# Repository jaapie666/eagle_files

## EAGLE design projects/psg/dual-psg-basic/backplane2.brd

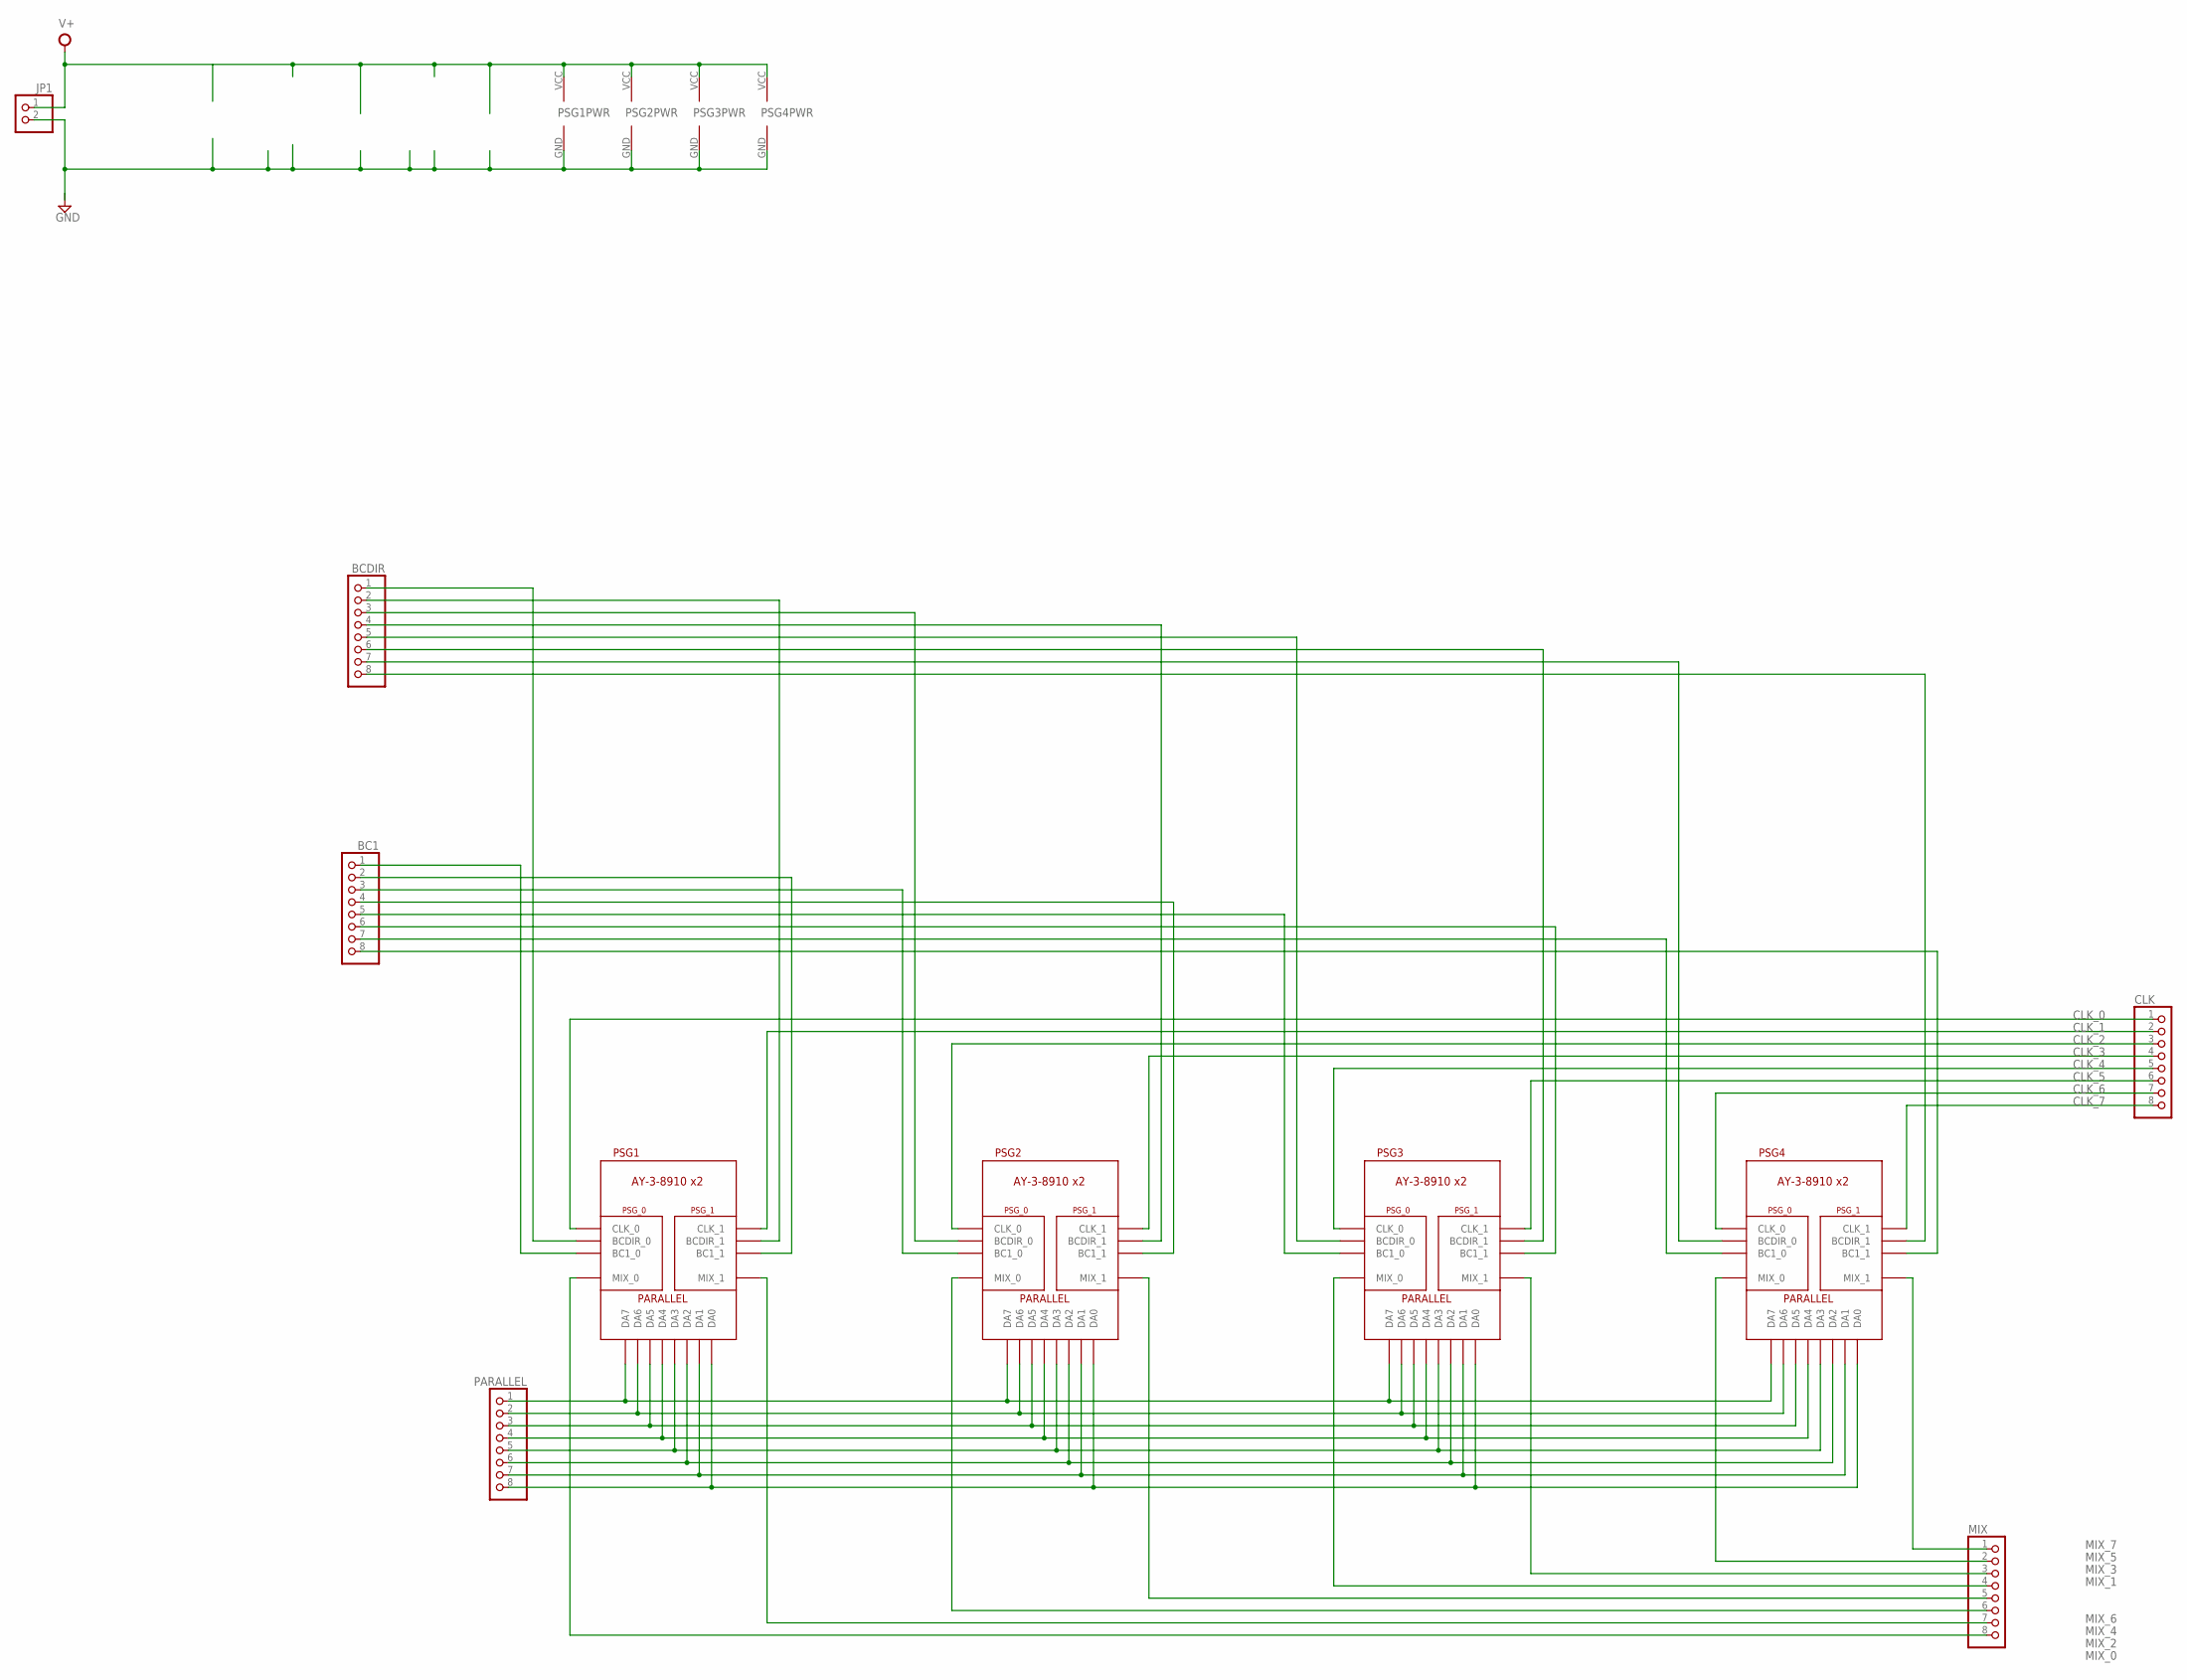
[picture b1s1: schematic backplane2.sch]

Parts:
BC1: PINHD-1X8; 1X08
BCDIR: PINHD-1X8; 1X08
CLK: PINHD-1X8; 1X08
JP1: PINHD-1X2; 1X02
MIX: PINHD-1X8; 1X08
PARALLEL: PINHD-1X8; 1X08
PSG1, PSG2, PSG3, PSG4: DUAL_PSG_DAUGHTER

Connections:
3: BCDIR.4, PSG2.BCDIR_1
BC1_0: BC1.1, PSG1.BC1_0
BC1_1: BC1.2, PSG1.BC1_1
BC1_2: BC1.3, PSG2.BC1_0
BC1_3: BC1.4, PSG2.BC1_1
BC1_4: BC1.5, PSG3.BC1_0
BC1_5: BC1.6, PSG3.BC1_1
BC1_6: BC1.7, PSG4.BC1_0
BC1_7: BC1.8, PSG4.BC1_1
BCDIR_0: BCDIR.1, PSG1.BCDIR_0
BCDIR_1: BCDIR.2, PSG1.BCDIR_1
BCDIR_2: BCDIR.3, PSG2.BCDIR_0
BCDIR_4: BCDIR.5, PSG3.BCDIR_0
BCDIR_5: BCDIR.6, PSG3.BCDIR_1
BCDIR_6: BCDIR.7, PSG4.BCDIR_0
BCDIR_7: BCDIR.8, PSG4.BCDIR_1
CLK_0: CLK.1, PSG1.CLK_0
CLK_1: CLK.2, PSG1.CLK_1
CLK_2: CLK.3, PSG2.CLK_0
CLK_3: CLK.4, PSG2.CLK_1
CLK_4: CLK.5, PSG3.CLK_0
CLK_5: CLK.6, PSG3.CLK_1
CLK_6: CLK.7, PSG4.CLK_0
CLK_7: CLK.8, PSG4.CLK_1
DA0: PARALLEL.8, PSG1.DA0, PSG2.DA0, PSG3.DA0, PSG4.DA0
DA1: PARALLEL.7, PSG1.DA1, PSG2.DA1, PSG3.DA1, PSG4.DA1
DA2: PARALLEL.6, PSG1.DA2, PSG2.DA2, PSG3.DA2, PSG4.DA2
DA3: PARALLEL.5, PSG1.DA3, PSG2.DA3, PSG3.DA3, PSG4.DA3
DA4: PARALLEL.4, PSG1.DA4, PSG2.DA4, PSG3.DA4, PSG4.DA4
DA5: PARALLEL.3, PSG1.DA5, PSG2.DA5, PSG3.DA5, PSG4.DA5
DA6: PARALLEL.2, PSG1.DA6, PSG2.DA6, PSG3.DA6, PSG4.DA6
DA7: PARALLEL.1, PSG1.DA7, PSG2.DA7, PSG3.DA7, PSG4.DA7
GND: JP1.2, PSG1.GND, PSG2.GND, PSG3.GND, PSG4.GND
MIX_0: MIX.8, PSG1.MIX_0
MIX_1: MIX.7, PSG1.MIX_1
MIX_2: MIX.6, PSG2.MIX_0
MIX_3: MIX.5, PSG2.MIX_1
MIX_4: MIX.4, PSG3.MIX_0
MIX_5: MIX.3, PSG3.MIX_1
MIX_6: MIX.2, PSG4.MIX_0
MIX_7: MIX.1, PSG4.MIX_1
V+: JP1.1, PSG1.VCC, PSG2.VCC, PSG3.VCC, PSG4.VCC

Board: 2 copper layers, 10 parts (0 on the bottom side), 42 nets, no tracks yet.

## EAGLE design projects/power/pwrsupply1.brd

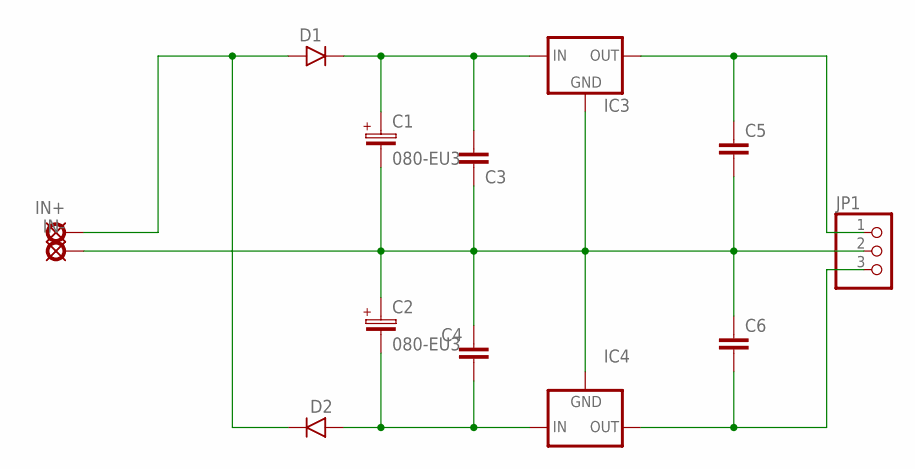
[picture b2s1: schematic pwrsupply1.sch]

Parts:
C1, C2: 080-EU3; 080_035_3
C3, C4: 070X0303; 070X030_3
C5: 070X0305; 070X030_5
C6: 070X0302; 070X030
D1, D2: 1N400X.4; DO41-4
IC3: 78XXL
IC4: 79XXL
IN+: PAD8; OCTOGON
IN-: PAD8; OCTOGON
JP1: PINHD-1X3; 1X03

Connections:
+15: C5.1, IC3.OUT, JP1.1
-15: C6.2, IC4.OUT, JP1.3
GND: C1.-, C2.+, C3.1, C4.1, C5.2, C6.1, IC3.GND, IC4.GND, IN-.1, JP1.2
unnamed: D1.A, D2.C, IN+.1
unnamed: C1.+, C3.2, D1.C, IC3.IN
unnamed: C2.-, C4.2, D2.A, IC4.IN

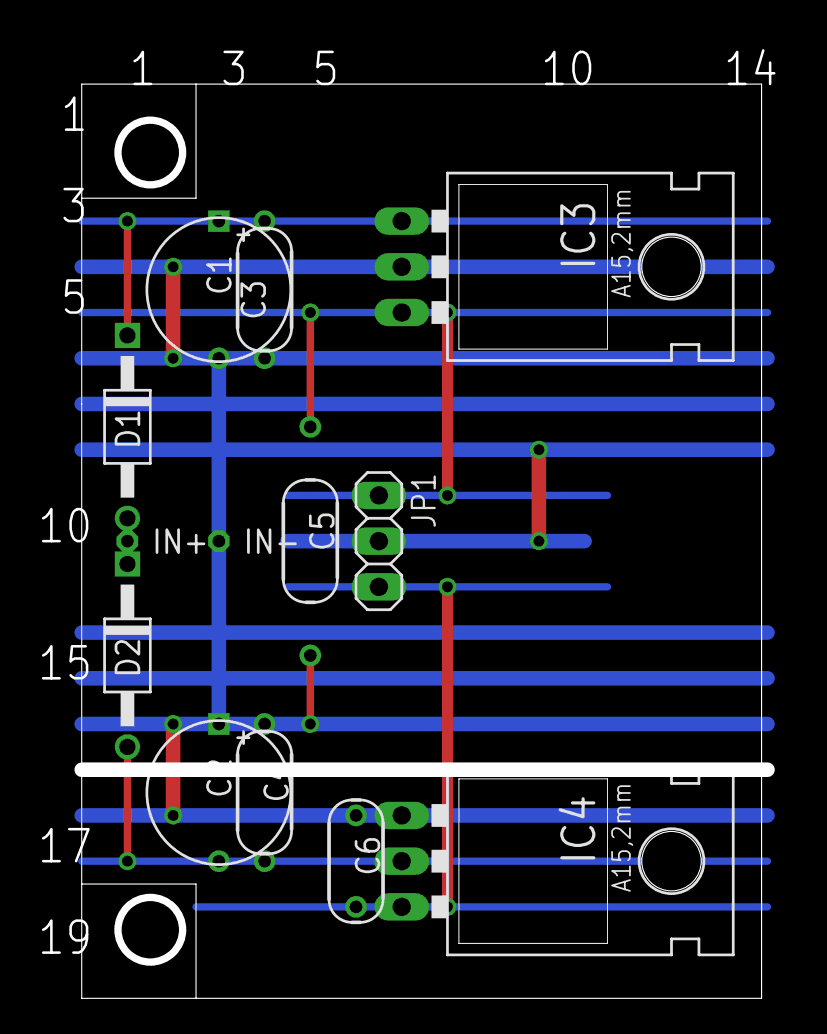
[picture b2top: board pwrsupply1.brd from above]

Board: 2 copper layers, 37.8 x 50.8 mm, 13 parts (0 on the bottom side), 6 nets.

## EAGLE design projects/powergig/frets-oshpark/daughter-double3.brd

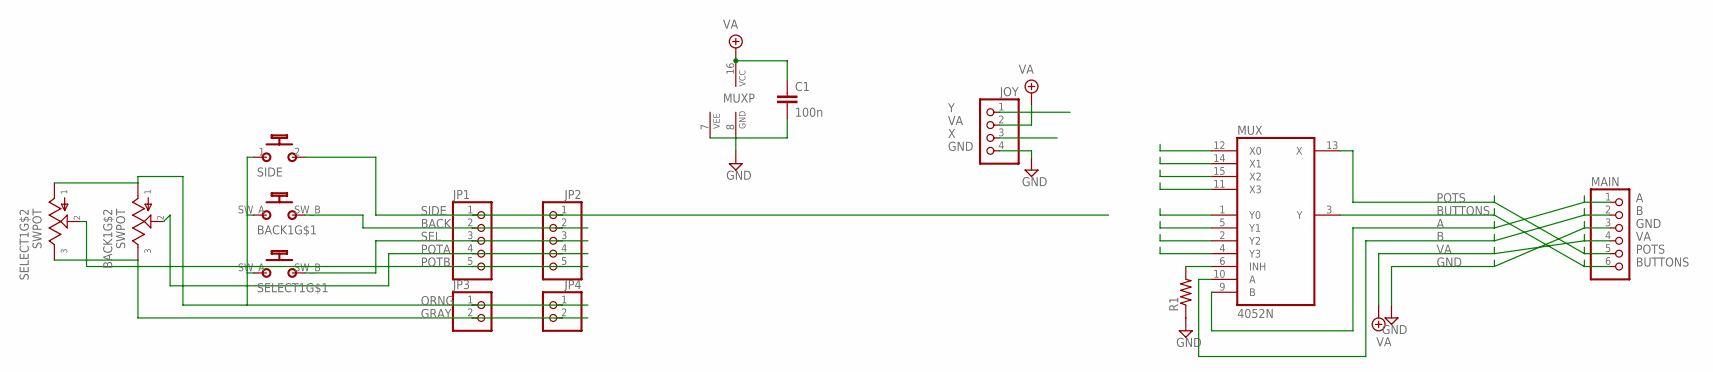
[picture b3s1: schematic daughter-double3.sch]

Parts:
BACK1: SWPOT
C1: 100n; 050X030_050_3
JOY: PINHD-1X4; 1X04
JP1, JP2: PINHD-1X5; 1X05
JP3, JP4: PINHD-1X2; 1X02
MAIN: PINHD-1X6; 1X06
MUX: 4052N; DIL16
R1: 6MM.1; R0207/1V
SELECT1: SWPOT
SIDE: MOMENTARYSPST1; SPST

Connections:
A: MAIN.1, MUX.9 (B)
B: MAIN.2, MUX.10 (A)
BACK: BACK1.SW_B (B_B), JP1.2, JP2.2
BUTTONS: MAIN.6, MUX.3 (Y)
GND: C1.2, JOY.4, MAIN.3, MUX.7 (VEE), MUX.8 (GND), R1.1
GRAY: BACK1.POT_A, JP3.2, JP4.2, SELECT1.POT_A
unnamed: MUX.6 (INH), R1.2
ORNG: BACK1.POT_B, BACK1.SW_A (B_A), JP3.1, JP4.1, SELECT1.POT_B, SELECT1.SW_A (B_A), SIDE.1
POTA: BACK1.POT_W, JP1.4, JP2.4
POTB: JP1.5, JP2.5, SELECT1.POT_W
POTS: MAIN.5, MUX.13 (X)
SEL: JP1.3, JP2.3, SELECT1.SW_B (B_B)
SIDE: JP2.1, SIDE.2 (S)
VA: C1.1, JOY.2, MAIN.4, MUX.16 (VCC)
X: JOY.1
Y: JOY.3

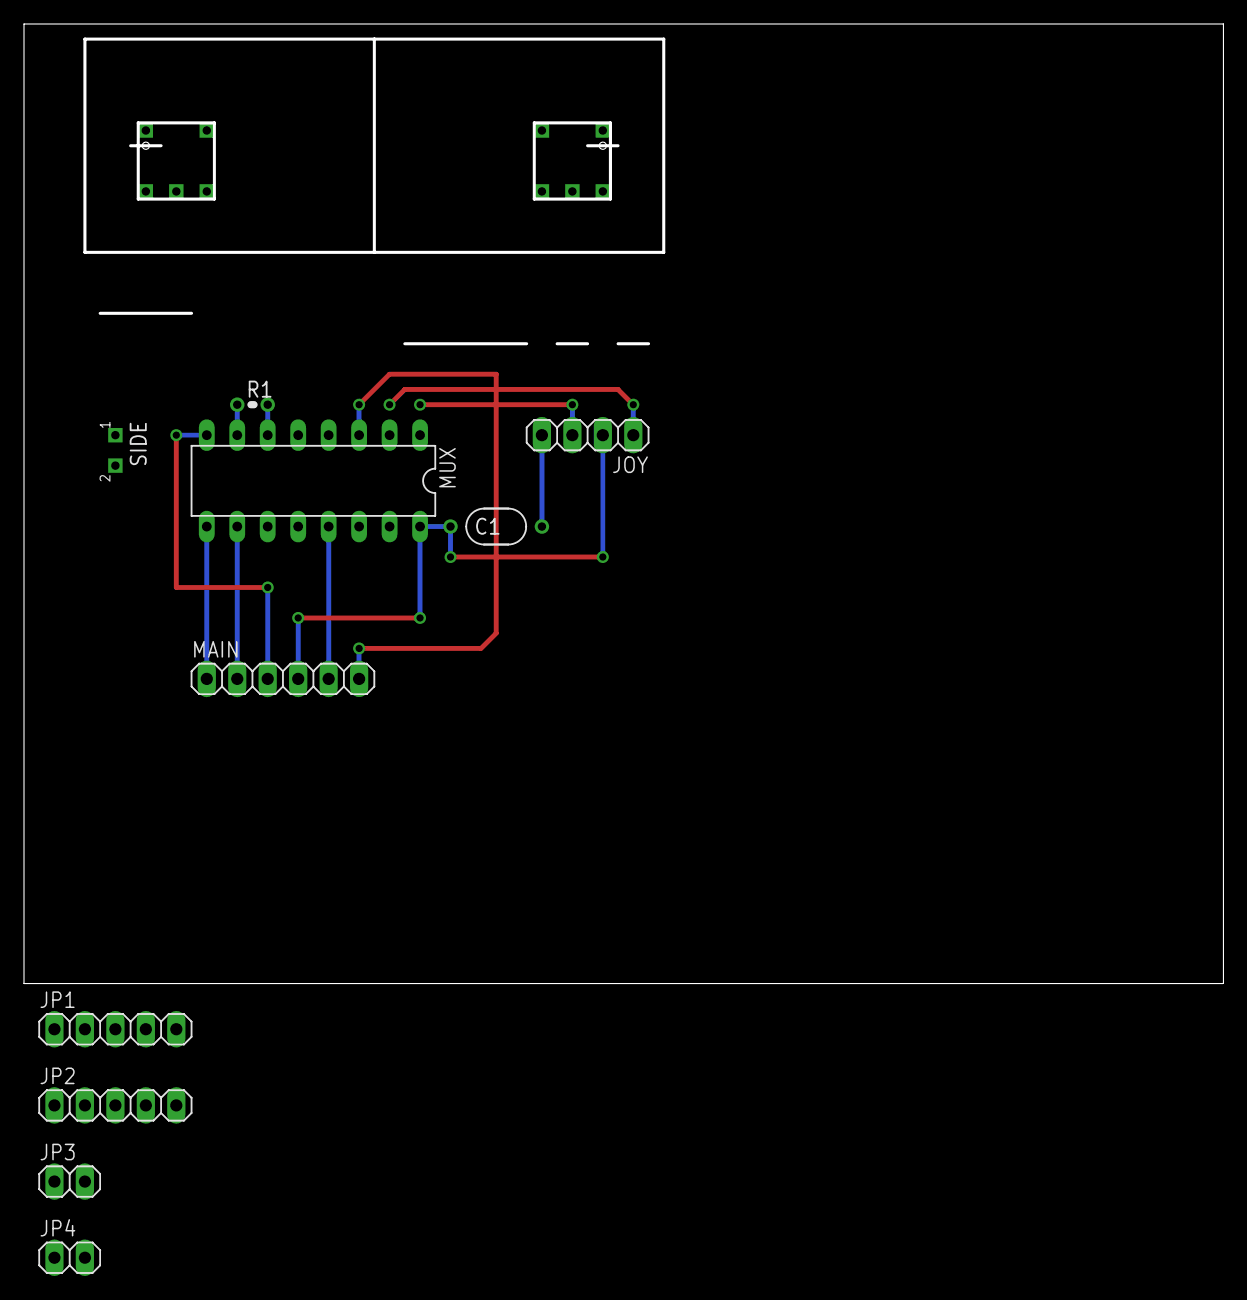
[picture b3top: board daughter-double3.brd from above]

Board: 2 copper layers, 100.0 x 80.0 mm, 12 parts (0 on the bottom side), 14 nets.

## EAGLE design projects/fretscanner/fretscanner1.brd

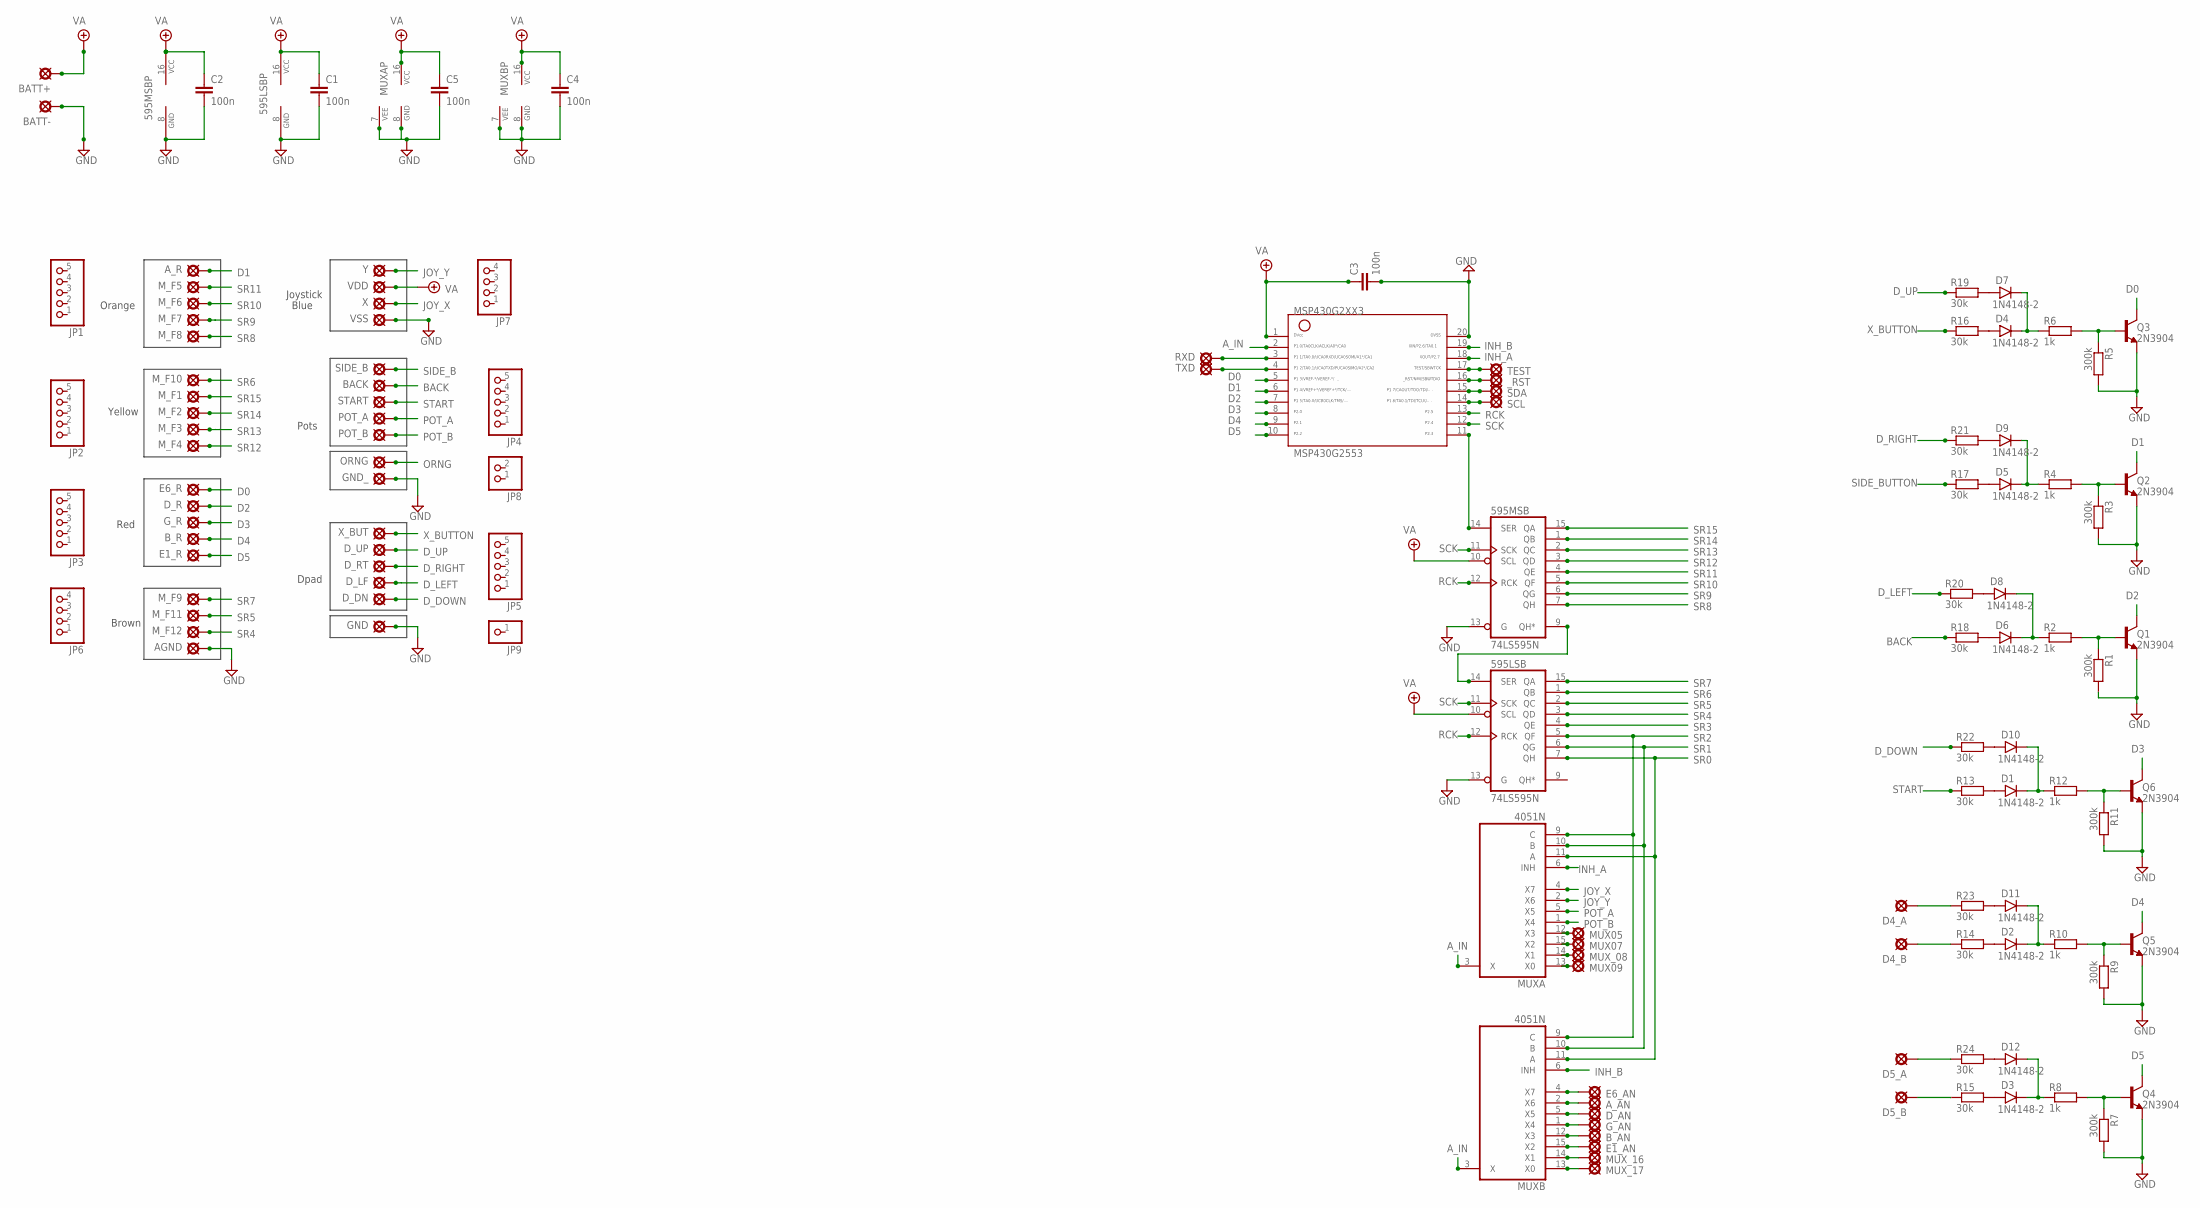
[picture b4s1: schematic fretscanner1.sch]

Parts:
595LSB, 595MSB: 74LS595N; DIL16
AGND: PAD; SQUARE
A_AN: PAD; SQUARE
A_R: PAD8; OCTOGON
BACK: PAD8; OCTOGON
BATT+: PADL; LONG
BATT-: PADL; LONG
B_AN: PAD; SQUARE
B_R: PAD8; OCTOGON
C1, C2, C3, C4, C5: 100n; 050X030_050_3
D1, D2, D3, D4, D5, D6, D7, D8, D9, D10, D11, D12: 1N4148-2; DO35-2
D4_A, D4_B, D5_A, D5_B: PAD; SQUARE
D_AN: PAD; SQUARE
D_DN: PAD; SQUARE
D_LF: PAD8; OCTOGON
D_R: PAD8; OCTOGON
D_RT: PAD8; OCTOGON
D_UP: PAD8; OCTOGON
E1_AN, E6_AN, E6_R: PAD; SQUARE
E1_R: PAD8; OCTOGON
GND: PAD; SQUARE
GND_: PAD8; OCTOGON
G_AN: PAD; SQUARE
G_R: PAD8; OCTOGON
JP1, JP2, JP3, JP4, JP5: PINHD-1X5; 1X05
JP6, JP7: PINHD-1X4; 1X04
JP8: PINHD-1X2; 1X02
JP9: PINHD-1X1; 1X01
MSP430G2553: G2XX3---N20; N20
MUX05, MUX07, MUX09: PAD; SQUARE
MUXA: 4051N; DIL16
MUXB: 4051N; DIL16
MUX_08, MUX_16, MUX_17: PAD; SQUARE
M_F1, M_F2, M_F3, M_F5, M_F6, M_F7, M_F9, M_F10, M_F11, M_F12: PAD8; OCTOGON
M_F4, M_F8: PAD; SQUARE
ORNG: PAD8; OCTOGON
POT_A: PAD8; OCTOGON
POT_B: PAD; SQUARE
Q1, Q2, Q3, Q4, Q5, Q6: 2N3904; TO92-
R1, R3, R5, R7, R9, R11: 300k; R0207/3
R2, R4, R6, R8, R10, R12: 1k; R0207/3
R13, R14, R15, R16, R17, R18, R19, R20, R21, R22, R23, R24: 30k; R0207/3
RXD: PAD; SQUARE
SCL: PAD; SQUARE
SDA: PAD8; OCTOGON
SIDE_B: PAD8; OCTOGON
START: PAD8; OCTOGON
TEST: PAD8; OCTOGON
TXD: PAD8; OCTOGON
VDD: PAD8; OCTOGON
VSS: PAD8; OCTOGON
X: PAD8; OCTOGON
X_BUT: PAD8; OCTOGON
Y: PAD; SQUARE
_RST: PAD; SQUARE

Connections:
A_AN: A_AN.1, MUXB.2 (X6)
A_IN: MSP430G2553.2, MUXA.3 (X), MUXB.3 (X)
BACK: BACK.1, R18.1
B_AN: B_AN.1, MUXB.12 (X3)
D0: E6_R.1, MSP430G2553.5, Q3.1 (C)
D1: A_R.1, MSP430G2553.6, Q2.1 (C)
D2: D_R.1, MSP430G2553.7, Q1.1 (C)
D3: G_R.1, MSP430G2553.8, Q6.1 (C)
D4: B_R.1, MSP430G2553.9, Q5.1 (C)
D5: E1_R.1, MSP430G2553.10, Q4.1 (C)
D_AN: D_AN.1, MUXB.5 (X5)
D_DOWN: D_DN.1, R22.1
D_LEFT: R20.1
D_RIGHT: D_RT.1, R21.1
D_UP: D_UP.1, R19.1
E1_AN: E1_AN.1, MUXB.15 (X2)
E6_AN: E6_AN.1, MUXB.4 (X7)
GND: 595LSB.8 (GND), 595LSB.13 (G), 595MSB.8 (GND), 595MSB.13 (G), BATT-.1, C1.2, C2.2, C3.2, C4.2, C5.2, GND.1, GND_.1, MSP430G2553.20, MUXA.7 (VEE), MUXA.8 (GND), MUXB.7 (VEE), MUXB.8 (GND), Q1.3 (E), Q2.3 (E), Q3.3 (E), Q4.3 (E), Q5.3 (E), Q6.3 (E), R1.2, R3.2, R5.2, R7.2, R9.2, R11.2, VSS.1
G_AN: G_AN.1, MUXB.1 (X4)
INH_A: MSP430G2553.18, MUXA.6 (INH)
INH_B: MSP430G2553.19, MUXB.6 (INH)
JOY_X: MUXA.4 (X7), X.1
JOY_Y: MUXA.2 (X6), Y.1
MUX05: MUX05.1, MUXA.12 (X3)
MUX07: MUX07.1, MUXA.15 (X2)
MUX08: MUXA.14 (X1), MUX_08.1
MUX09: MUX09.1, MUXA.13 (X0)
MUX16: MUXB.14 (X1), MUX_16.1
MUX17: MUXB.13 (X0), MUX_17.1
unnamed: 595LSB.14 (SER), 595MSB.9 (QH*)
unnamed: Q2.2 (B), R3.1, R4.2
unnamed: D3.A, R15.2
unnamed: D5.C, D9.C, R4.1
unnamed: Q3.2 (B), R5.1, R6.2
unnamed: Q1.2 (B), R1.1, R2.2
unnamed: D6.C, D8.C, R2.1
unnamed: D4.A, R16.2
unnamed: D5.A, R17.2
unnamed: D4.C, D7.C, R6.1
unnamed: Q4.2 (B), R7.1, R8.2
unnamed: D6.A, R18.2
unnamed: D3.C, D12.C, R8.1
unnamed: Q5.2 (B), R9.1, R10.2
unnamed: D1.A, R13.2
unnamed: D2.C, D11.C, R10.1
unnamed: Q6.2 (B), R11.1, R12.2
unnamed: D2.A, R14.2
unnamed: D1.C, D10.C, R12.1
unnamed: D7.A, R19.2
unnamed: D8.A, R20.2
unnamed: D9.A, R21.2
unnamed: D10.A, R22.2
unnamed: D4_B.1, R14.1
unnamed: D5_B.1, R15.1
unnamed: D11.A, R23.2
unnamed: D12.A, R24.2
unnamed: D4_A.1, R23.1
unnamed: D5_A.1, R24.1
ORNG: ORNG.1
POT_A: MUXA.5 (X5)
POT_B: MUXA.1 (X4), POT_B.1
RCK: 595LSB.12 (RCK), 595MSB.12 (RCK), MSP430G2553.13
RXD: MSP430G2553.3, RXD.1
SCK: 595LSB.11 (SCK), 595MSB.11 (SCK), MSP430G2553.12
SCL: MSP430G2553.14, SCL.1
SDA: MSP430G2553.15, SDA.1
SER: 595MSB.14 (SER), MSP430G2553.11
SIDE_B: SIDE_B.1
SIDE_BUTTON: R17.1
SR0: 595LSB.7 (QH), MUXA.11 (A), MUXB.11 (A)
SR1: 595LSB.6 (QG), MUXA.10 (B), MUXB.10 (B)
SR2: 595LSB.5 (QF), MUXA.9 (C), MUXB.9 (C)
SR3: 595LSB.4 (QE)
SR4: 595LSB.3 (QD), M_F12.1
SR5: 595LSB.2 (QC), M_F11.1
SR6: 595LSB.1 (QB), M_F10.1
SR7: 595LSB.15 (QA), M_F9.1
SR8: 595MSB.7 (QH), M_F8.1
SR9: 595MSB.6 (QG)
SR10: 595MSB.5 (QF), M_F6.1
SR11: 595MSB.4 (QE), M_F5.1
SR12: 595MSB.3 (QD), M_F4.1
SR13: 595MSB.2 (QC)
SR14: 595MSB.1 (QB), M_F2.1
SR15: 595MSB.15 (QA), M_F1.1
START: R13.1, START.1
TEST: MSP430G2553.17, TEST.1
TXD: MSP430G2553.4, TXD.1
VA: 595LSB.10 (SCL), 595LSB.16 (VCC), 595MSB.10 (SCL), 595MSB.16 (VCC), BATT+.1, C1.1, C2.1, C3.1, C4.1, C5.1, MSP430G2553.1, MUXA.16 (VCC), MUXB.16 (VCC), VDD.1
X_BUTTON: R16.1, X_BUT.1
_RST: MSP430G2553.16, _RST.1

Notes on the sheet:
Yellow
Orange
Red
Brown
Joystick
Pots
Dpad
Blue

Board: 2 copper layers, 121 parts (0 on the bottom side), 83 nets, no tracks yet.

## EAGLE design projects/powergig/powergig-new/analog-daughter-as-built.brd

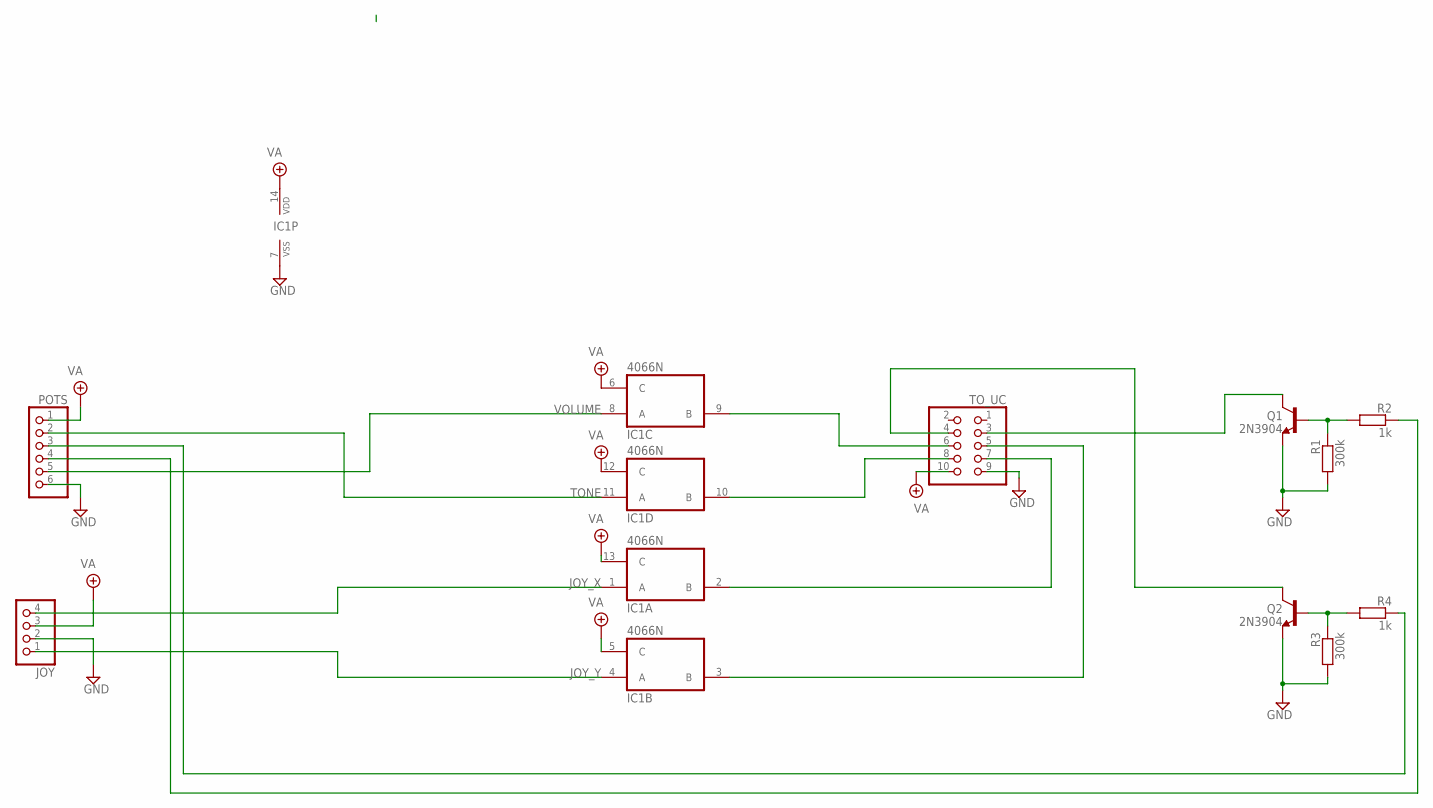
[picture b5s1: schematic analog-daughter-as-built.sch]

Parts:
IC1: 4066N; DIL14
JOY: PINHD-1X4; 1X04
POTS: PINHD-1X6; 1X06
Q1, Q2: 2N3904; TO92-
R1, R3: 300k; R0207/1V
R2, R4: 1k; R0207/1V
TO_UC: PINHD-2X5; 2X05

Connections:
GND: IC1.7 (VSS), JOY.2, POTS.6, Q1.3 (E), Q2.3 (E), R1.2, R3.2, TO_UC.9
JOY_X: IC1.1 (A), JOY.4
JOY_Y: IC1.4 (A), JOY.1
unnamed: Q1.1 (C), TO_UC.3
unnamed: IC1.9 (B), TO_UC.6
unnamed: IC1.10 (B), TO_UC.8
unnamed: IC1.2 (B), TO_UC.7
unnamed: IC1.3 (B), TO_UC.5
unnamed: Q2.1 (C), TO_UC.4
unnamed: Q1.2 (B), R1.1, R2.2
unnamed: Q2.2 (B), R3.1, R4.2
TONE: IC1.11 (A), POTS.2
TONE_BUTTON: POTS.3, R4.1
VA: IC1.5 (C), IC1.6 (C), IC1.12 (C), IC1.13 (C), IC1.14 (VDD), JOY.3, POTS.1, TO_UC.10
VOLUME: IC1.8 (A), POTS.5
VOL_BUTTON: POTS.4, R2.1

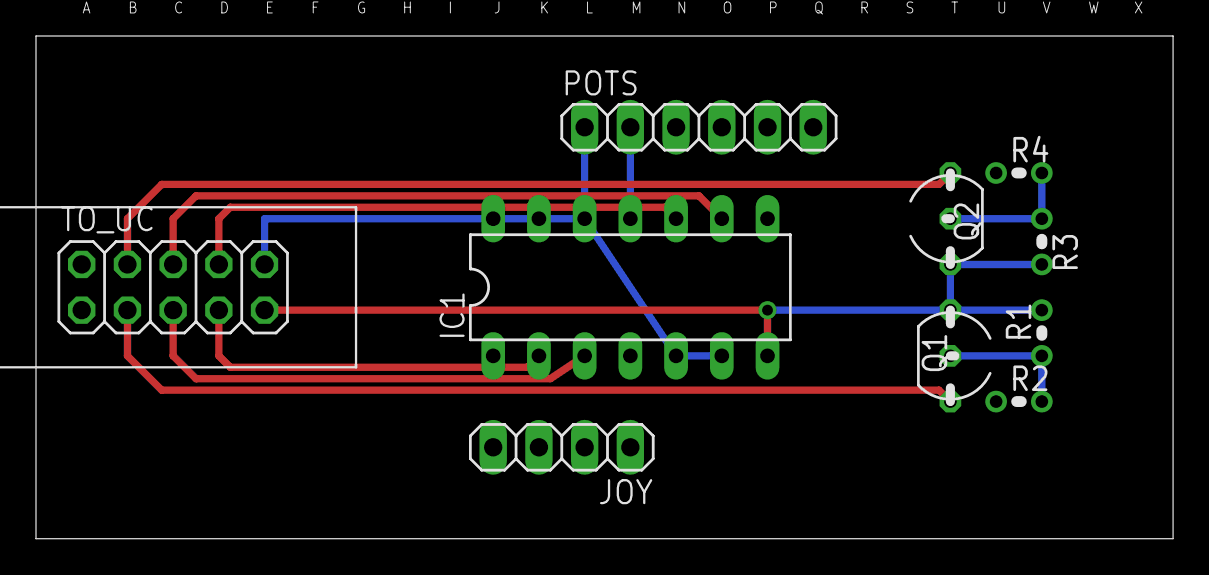
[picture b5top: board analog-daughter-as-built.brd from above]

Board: 2 copper layers, 63.2 x 27.9 mm, 10 parts (0 on the bottom side), 16 nets.

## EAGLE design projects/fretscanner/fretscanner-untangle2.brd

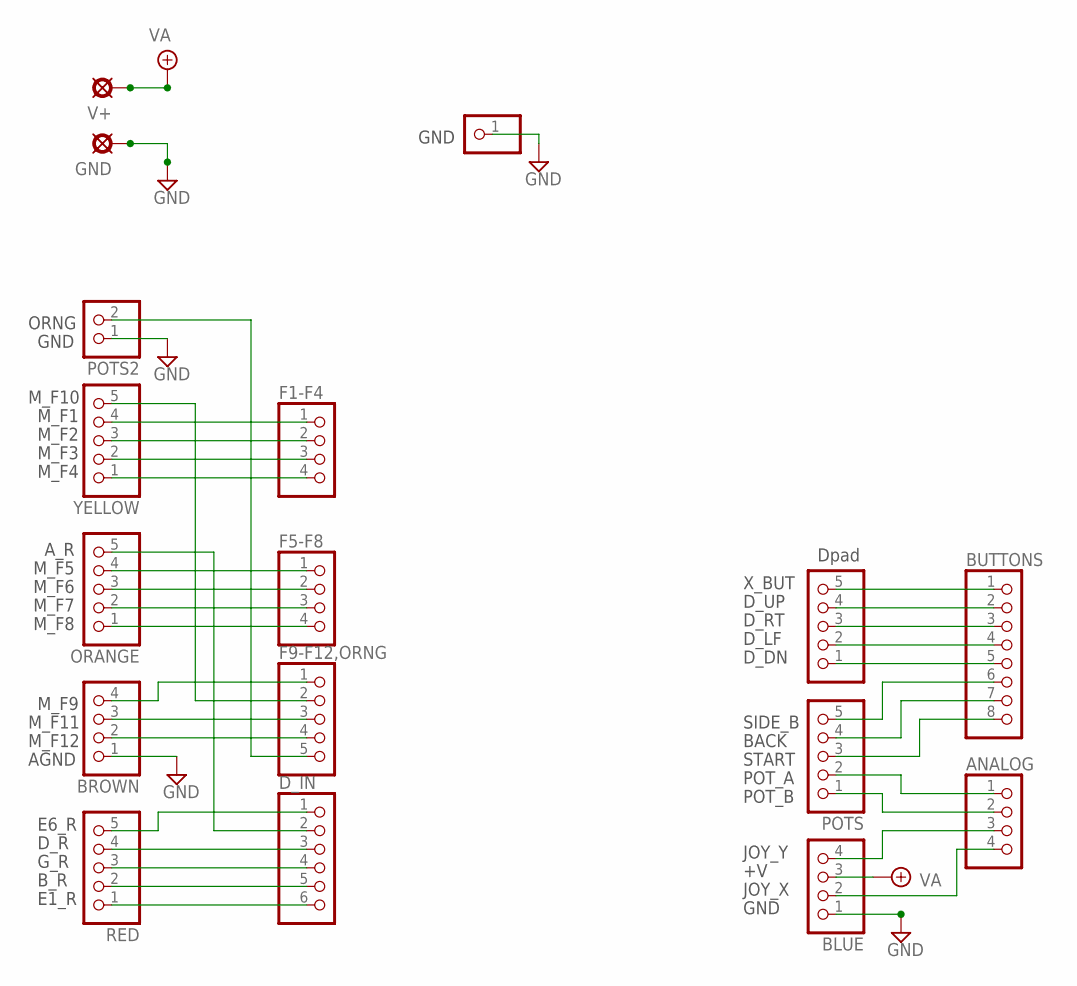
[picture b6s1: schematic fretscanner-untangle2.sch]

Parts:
ANALOG: PINHD-1X4; 1X04
BLUE: PINHD-1X4; 1X04
BROWN: PINHD-1X4; 1X04
BUTTONS: PINHD-1X8; 1X08
DPAD: PINHD-1X5; 1X05
DPAD2: PINHD-1X1; 1X01
D_IN: PINHD-1X6; 1X06
F1-F4, F5-F8: PINHD-1X4; 1X04
F9-F12,ORNG: PINHD-1X5; 1X05
GND: PADL; LONG
ORANGE: PINHD-1X5; 1X05
POTS: PINHD-1X5; 1X05
POTS2: PINHD-1X2; 1X02
RED: PINHD-1X5; 1X05
V+: PADL; LONG
YELLOW: PINHD-1X5; 1X05

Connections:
BACK: BUTTONS.7, POTS.4
D0: D_IN.1, RED.5
GND: BLUE.1, BROWN.1, DPAD2.1, GND.1, POTS2.1
JOY_X: ANALOG.4, BLUE.2
JOY_Y: ANALOG.3, BLUE.4
unnamed: F1-F4.1, YELLOW.4
unnamed: F1-F4.2, YELLOW.3
unnamed: F1-F4.3, YELLOW.2
unnamed: F1-F4.4, YELLOW.1
unnamed: F5-F8.1, ORANGE.4
unnamed: F5-F8.2, ORANGE.3
unnamed: F5-F8.3, ORANGE.2
unnamed: F5-F8.4, ORANGE.1
unnamed: BROWN.4, F9-F12,ORNG.1
unnamed: F9-F12,ORNG.2, YELLOW.5
unnamed: D_IN.3, RED.4
unnamed: D_IN.4, RED.3
unnamed: D_IN.2, ORANGE.5
unnamed: BROWN.3, F9-F12,ORNG.3
unnamed: BROWN.2, F9-F12,ORNG.4
unnamed: F9-F12,ORNG.5, POTS2.2
unnamed: D_IN.5, RED.2
unnamed: D_IN.6, RED.1
unnamed: BUTTONS.1, DPAD.5
unnamed: BUTTONS.2, DPAD.4
unnamed: BUTTONS.3, DPAD.3
unnamed: BUTTONS.4, DPAD.2
unnamed: BUTTONS.5, DPAD.1
POT_A: ANALOG.1, POTS.2
POT_B: ANALOG.2, POTS.1
SIDE_B: BUTTONS.6, POTS.5
START: BUTTONS.8, POTS.3
VA: BLUE.3, V+.1

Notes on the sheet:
Dpad
A_R
M_F5
M_F6
M_F7
M_F8
M_F10
M_F1
M_F2
M_F3
M_F4
M_F9
M_F11
M_F12
AGND
E6_R
D_R
G_R
B_R
E1_R
X_BUT
D_UP
D_RT
D_LF
D_DN
GND
SIDE_B
BACK
START
POT_A
POT_B
ORNG
JOY_X
JOY_Y

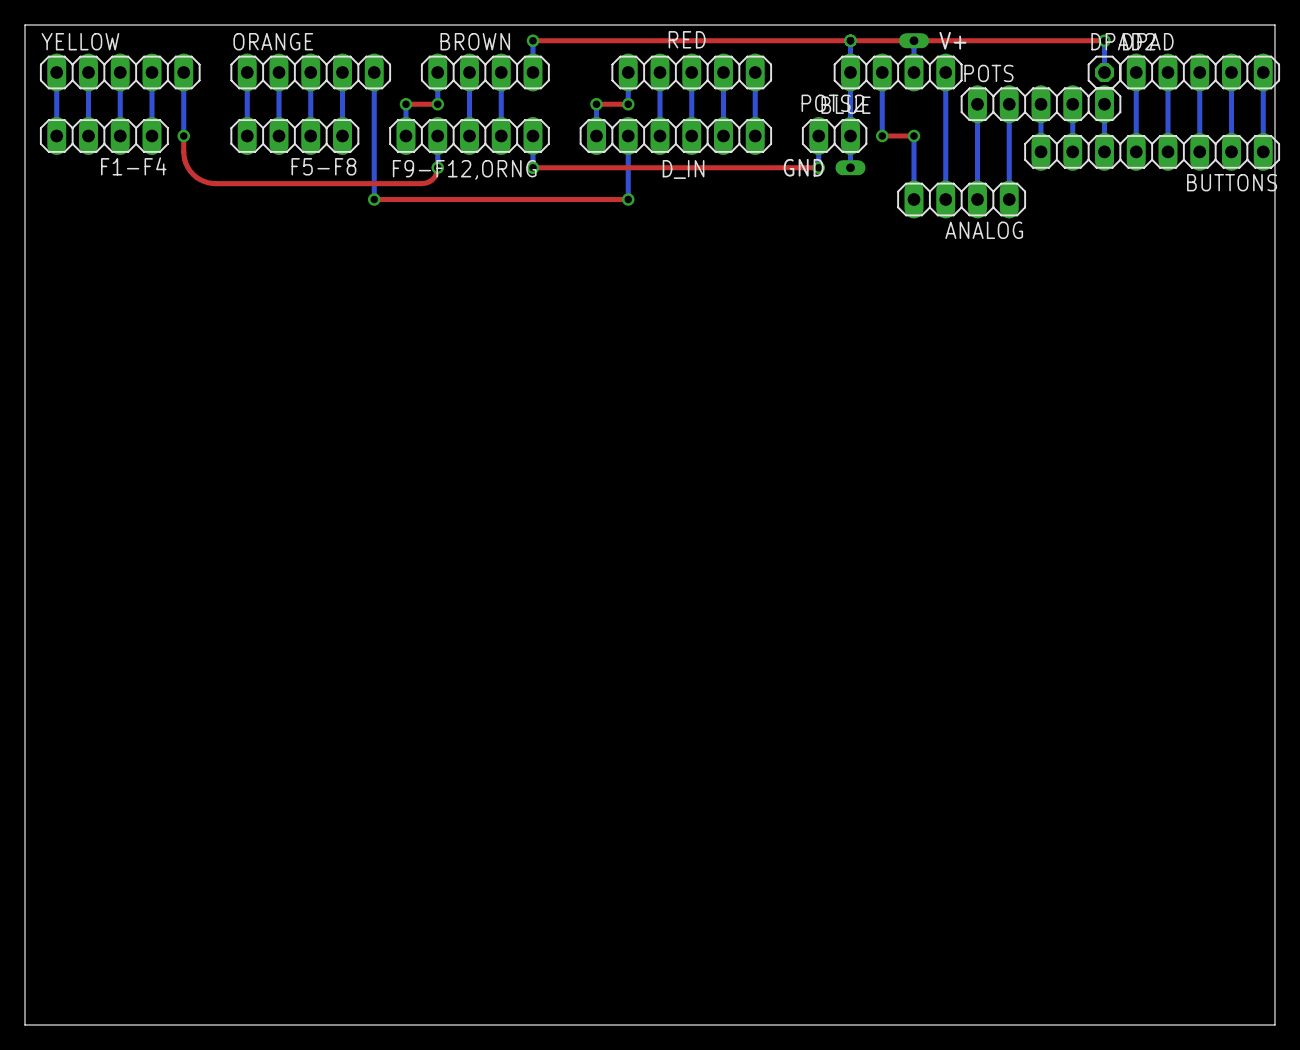
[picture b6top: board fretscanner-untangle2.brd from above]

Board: 2 copper layers, 100.0 x 80.0 mm, 17 parts (0 on the bottom side), 33 nets.

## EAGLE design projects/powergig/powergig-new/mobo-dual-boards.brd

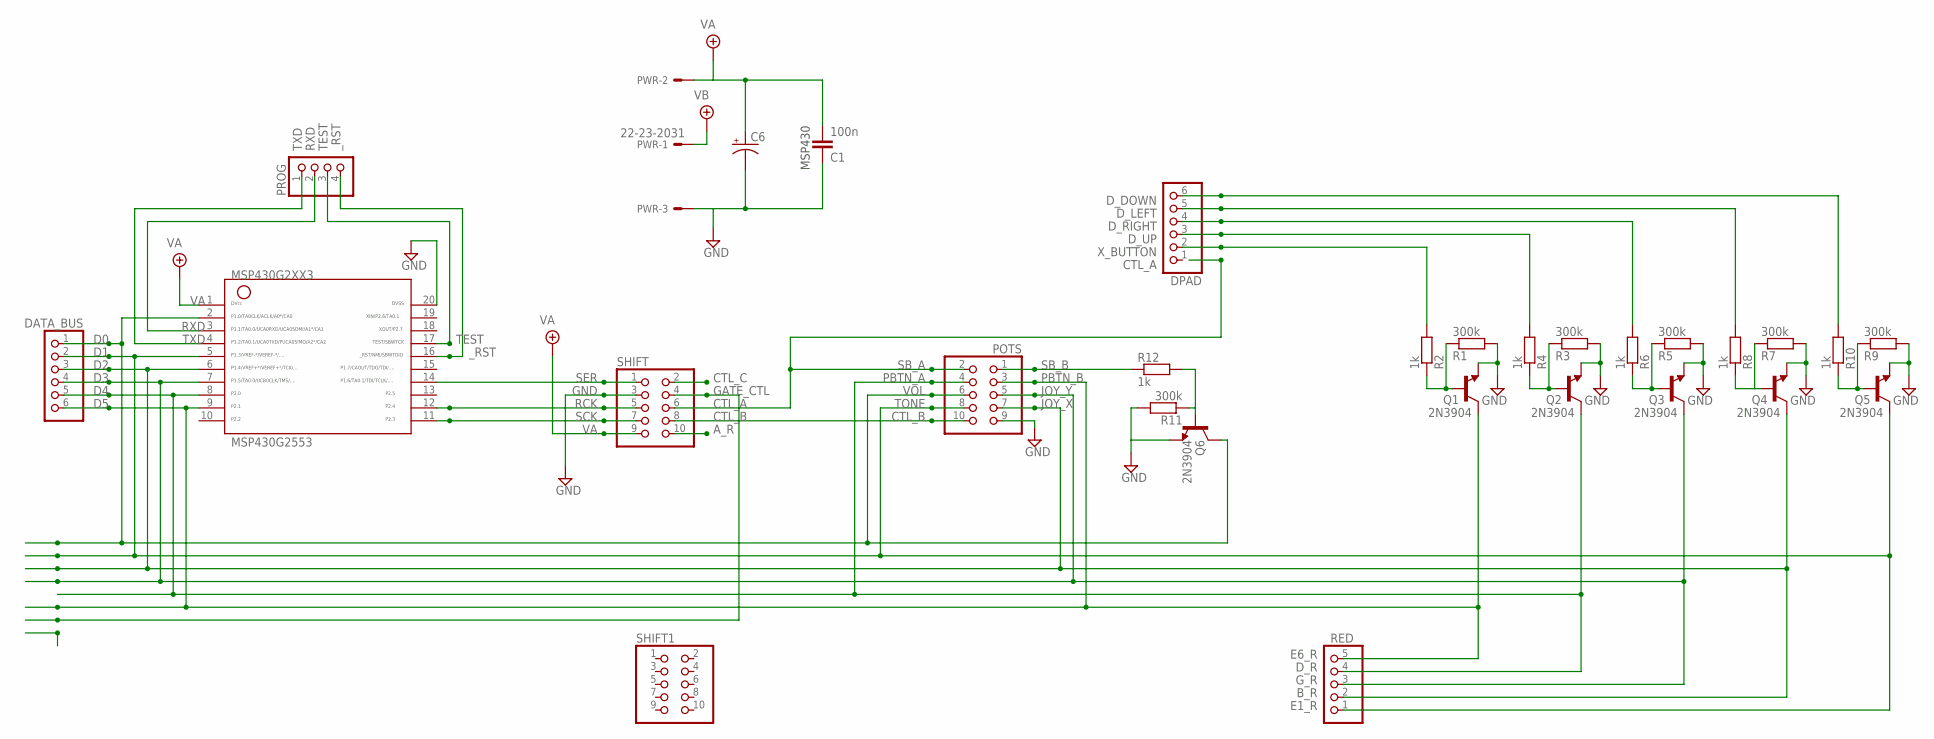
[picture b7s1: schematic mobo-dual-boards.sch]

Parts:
C1: 100n; 050X030_050_3
C6: 0501; 050_020_1
DATA_BUS: PINHD-1X6; 1X06
DPAD: PINHD-1X6; 1X06
MSP430G2553: G2XX3---N20; N20
POTS: PINHD-2X5; 2X05
PROG: PINHD-1X4; 1X04
PWR: 22-23-2031
Q1, Q2, Q3, Q4, Q5, Q6: 2N3904; TO92-
R1, R3, R5, R7, R9, R11: 300k; R0207/1V
R2, R4, R6, R8, R10, R12: 1k; R0207/1V
RED: PINHD-1X5; 1X05
SHIFT, SHIFT1: PINHD-2X5; 2X05

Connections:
CTL_A: POTS.2, SHIFT.6
CTL_B: POTS.10, SHIFT.8
CTL_C: SHIFT.2
D0: DATA_BUS.1, MSP430G2553.2, POTS.6, Q6.1 (C), SHIFT.10
D1: DATA_BUS.2, MSP430G2553.5, POTS.8, Q5.1 (C), RED.1
D2: DATA_BUS.3, MSP430G2553.6, POTS.7, Q4.1 (C), RED.2
D3: DATA_BUS.4, MSP430G2553.7, POTS.5, Q3.1 (C), RED.3
D4: DATA_BUS.5, MSP430G2553.8, POTS.4, Q2.1 (C), RED.4
D5: DATA_BUS.6, MSP430G2553.9, POTS.3, Q1.1 (C), RED.5
D_DOWN: DPAD.6, R10.2
D_LEFT: DPAD.5, R8.2
D_RIGHT: DPAD.4, R6.2
D_UP: DPAD.3, R4.2
GATE_CTL: SHIFT.4
GND: C1.1, C6.-, MSP430G2553.20, POTS.9, PWR.3, Q1.3 (E), Q2.3 (E), Q3.3 (E), Q4.3 (E), Q5.3 (E), Q6.3 (E), R1.2, R3.2, R5.2, R7.2, R9.2, R11.2, SHIFT.3
unnamed: Q6.2 (B), R11.1, R12.2
unnamed: Q1.2 (B), R1.1, R2.1
unnamed: Q2.2 (B), R3.1, R4.1
unnamed: Q3.2 (B), R5.1, R6.1
unnamed: Q4.2 (B), R7.1, R8.1
unnamed: Q5.2 (B), R9.1, R10.1
unnamed: POTS.1, R12.1
RCK: MSP430G2553.12, SHIFT.5
RXD: MSP430G2553.3, PROG.2
SCK: MSP430G2553.11, SHIFT.7
SER: MSP430G2553.14, SHIFT.1
TEST: MSP430G2553.17, PROG.3
TXD: MSP430G2553.4, PROG.1
VA: C1.2, C6.+, MSP430G2553.1, PWR.2, SHIFT.9
VB: PWR.1
X_BUTTON: DPAD.2, R2.2
_RST: MSP430G2553.16, PROG.4

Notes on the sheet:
MSP430
A_R
E6_R
D_R
G_R
B_R
E1_R
TONE
VOL
PBTN_A
PBTN_B
JOY_X
JOY_Y
SB_A
CTL_B
SB_B
CTL_A

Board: 2 copper layers, 29 parts (0 on the bottom side), 29 nets, no tracks yet.
